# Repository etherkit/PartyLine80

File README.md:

# Party Line 80

## All-Discrete 80 Meter CW QRP Transceiver

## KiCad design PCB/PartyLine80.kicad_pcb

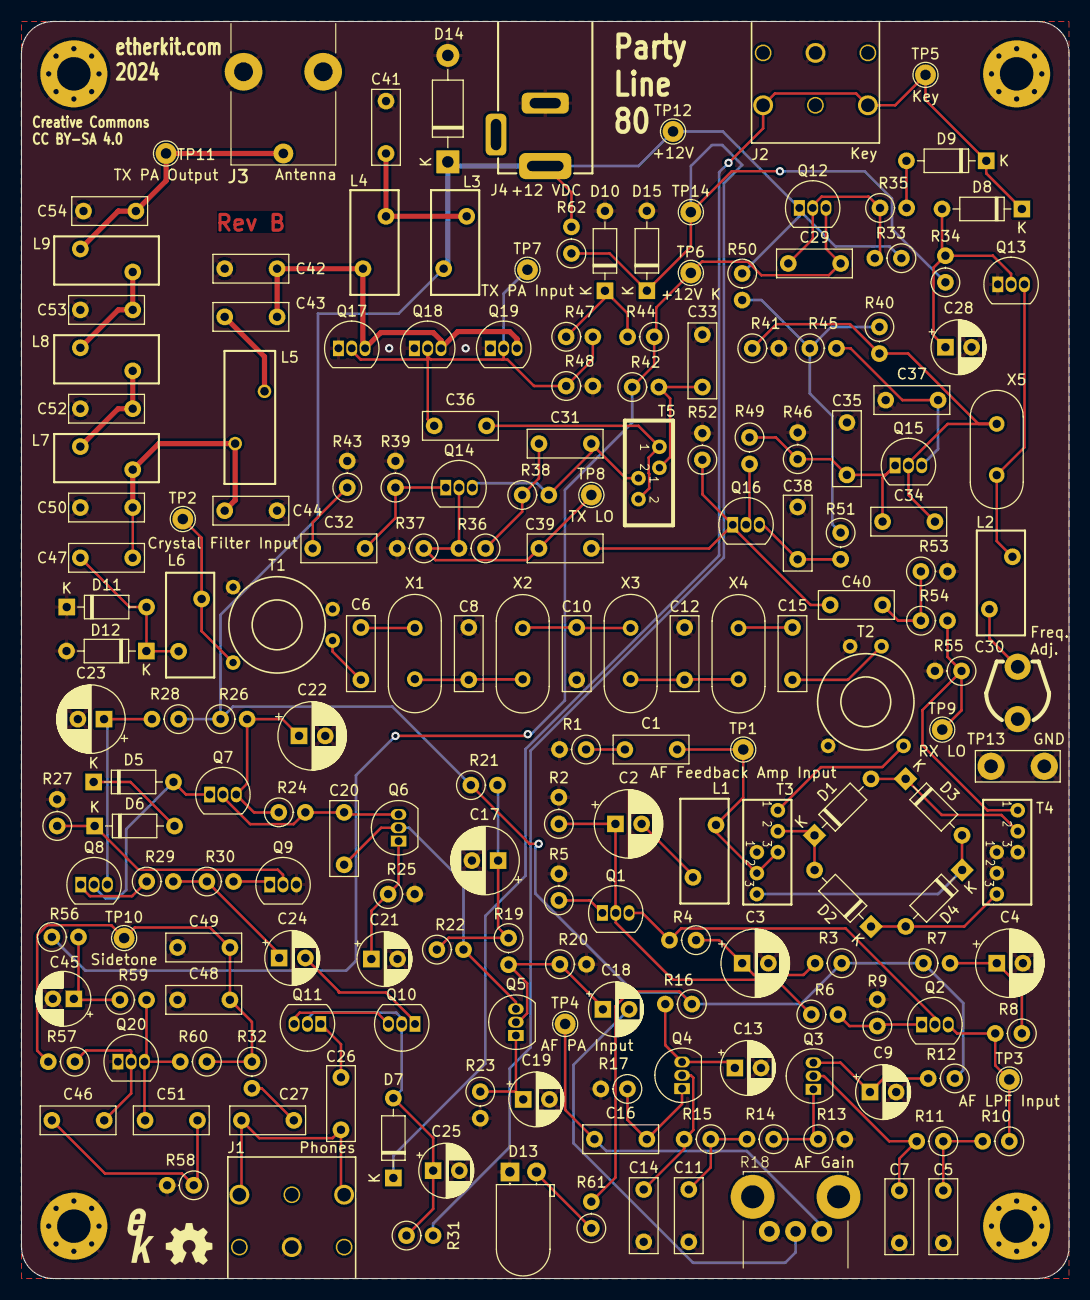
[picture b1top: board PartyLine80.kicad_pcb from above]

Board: 2 copper layers, 100.0 x 120.0 mm, 194 parts (0 on the bottom side), 95 nets.

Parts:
C1, C29, C31, C32, C33, C36, C37, C38, C39, C40, C41, C46, C48, C49, C51: 100n; C_Rect_L7.0mm_W2.5mm_P5.00mm
C2: 220u; CP_Radial_D6.3mm_P2.50mm
C3, C4, C17, C22, C23: 100u; CP_Radial_D6.3mm_P2.50mm
C5, C7, C11, C14: 10n; C_Rect_L7.0mm_W2.5mm_P5.00mm
C6, C10, C15: 25; C_Rect_L7.0mm_W2.5mm_P5.00mm
C8, C12: 20; C_Rect_L7.0mm_W2.5mm_P5.00mm
C9, C13, C19, C21, C24: 10u; CP_Radial_D5.0mm_P2.50mm
C16: 1u Film; C_Rect_L7.0mm_W2.5mm_P5.00mm
C18: 1u Film; CP_Radial_D5.0mm_P2.50mm
C20: 2.2n; C_Rect_L7.0mm_W2.5mm_P5.00mm
C25, C28: 1u; CP_Radial_D5.0mm_P2.50mm
C26, C27: 560n Film; C_Rect_L7.0mm_W2.5mm_P5.00mm
C30: 45p; TRIMCAP-MURATA
C34, C35, C42: 560p; C_Rect_L7.0mm_W2.5mm_P5.00mm
C43: 360p; C_Rect_L7.0mm_W2.5mm_P5.00mm
C44: 1.5n; C_Rect_L7.0mm_W2.5mm_P5.00mm
C45: 1u; CP_Radial_D5.0mm_P2.00mm
C47: 82p; C_Rect_L7.0mm_W2.5mm_P5.00mm
C50, C54: 270p; C_Rect_L7.0mm_W2.5mm_P5.00mm
C52, C53: 1n; C_Rect_L7.0mm_W2.5mm_P5.00mm
D1, D2, D3, D4, D5, D6, D7, D8, D9, D11, D12: 1N4148; D_DO-35_SOD27_P7.62mm_Horizontal
D10, D15: 1N5237B; D_DO-35_SOD27_P7.62mm_Horizontal
D13: LED; LED_D5.0mm_Horizontal_O1.27mm_Z3.0mm
D14: SB140; D_DO-41_SOD81_P10.16mm_Horizontal
G1: LOGO; EtherkitLogoSmall
H1, H2, H3, H4: MountingHole_Pad; MountingHole_3.2mm_M3_Pad_Via
J1: Phones; Kycon_STX-3120-3B
J2: Key; Kycon_STX-3120-3B
J3: BNC; Molex_0731713150
J4: 2.1 mm Barrel Jack; CUI_PJ-202AH
L1: FT37-43 25T; T37-V
L2: T37-2 22T; T37-V
L3, L4: FT37-43 10T; T37-V
L5: T50-2 36T; T50-V
L6: FT37-61 20T; T37-V
L7, L9: T37-2 20T; T37-V
L8: T37-2 26T; T37-V
Q1, Q2, Q3, Q4, Q5, Q6, Q7, Q8, Q14, Q15, Q16, Q20: 2N4401; TO-92_Inline
Q9, Q12: 2N4403; TO-92_Inline
Q10, Q11, Q13, Q17, Q18, Q19: 2N7000; TO-92_Inline
R1, R7, R26: 51; R_Axial_DIN0207_L6.3mm_D2.5mm_P2.54mm_Vertical
R2, R6: 1.8k; R_Axial_DIN0207_L6.3mm_D2.5mm_P2.54mm_Vertical
R3, R53, R55: 150; R_Axial_DIN0207_L6.3mm_D2.5mm_P2.54mm_Vertical
R4, R62: 1k; R_Axial_DIN0207_L6.3mm_D2.5mm_P2.54mm_Vertical
R5: 22; R_Axial_DIN0207_L6.3mm_D2.5mm_P2.54mm_Vertical
R8: 680; R_Axial_DIN0207_L6.3mm_D2.5mm_P2.54mm_Vertical
R9, R32, R33, R50, R52: 220; R_Axial_DIN0207_L6.3mm_D2.5mm_P2.54mm_Vertical
R10, R11, R13, R14, R15, R17, R21: 4.7k; R_Axial_DIN0207_L6.3mm_D2.5mm_P2.54mm_Vertical
R12, R16, R39, R45, R51: 100; R_Axial_DIN0207_L6.3mm_D2.5mm_P2.54mm_Vertical
R18: 1k Audio; Bournes_PTV09A
R19: 47k; R_Axial_DIN0207_L6.3mm_D2.5mm_P2.54mm_Vertical
R20, R40, R41, R44: 10k; R_Axial_DIN0207_L6.3mm_D2.5mm_P2.54mm_Vertical
R22, R24, R25, R35, R37: 2.2k; R_Axial_DIN0207_L6.3mm_D2.5mm_P2.54mm_Vertical
R23, R27, R46, R49: 470; R_Axial_DIN0207_L6.3mm_D2.5mm_P2.54mm_Vertical
R28: 10; R_Axial_DIN0207_L6.3mm_D2.5mm_P2.54mm_Vertical
R29, R30: 1; R_Axial_DIN0207_L6.3mm_D2.5mm_P2.54mm_Vertical
R31, R34: 100k; R_Axial_DIN0207_L6.3mm_D2.5mm_P2.54mm_Vertical
R36: 1.5k; R_Axial_DIN0207_L6.3mm_D2.5mm_P2.54mm_Vertical
R38: 3k; R_Axial_DIN0207_L6.3mm_D2.5mm_P2.54mm_Vertical
R42, R56: 47; R_Axial_DIN0207_L6.3mm_D2.5mm_P2.54mm_Vertical
R43: 4.7; R_Axial_DIN0207_L6.3mm_D2.5mm_P2.54mm_Vertical
R47, R48, R57, R59, R60, R61: 3.3k; R_Axial_DIN0207_L6.3mm_D2.5mm_P2.54mm_Vertical
R54: 36; R_Axial_DIN0207_L6.3mm_D2.5mm_P2.54mm_Vertical
R58: 330; R_Axial_DIN0207_L6.3mm_D2.5mm_P2.54mm_Vertical
SYM1: Logo_Open_Hardware_Small; OSHWLogo4mm
T1, T2: FT37-43 3T:21T; T37-STEPDOWN
T3, T4: FT37-43 10T Trifilar; T37-V-TRIFILARXFMR
T5: FT37-43 10T Bifilar; T37-V-BIFILARXFMR
TP1: AF Feedback Amp Input; TestPoint_THTPad_D2.0mm_Drill1.0mm
TP2: Crystal Filter Input; TestPoint_THTPad_D2.0mm_Drill1.0mm
TP3: AF LPF Input; TestPoint_THTPad_D2.0mm_Drill1.0mm
TP4: AF PA Input; TestPoint_THTPad_D2.0mm_Drill1.0mm
TP5: Key; TestPoint_THTPad_D2.0mm_Drill1.0mm
TP6: +12V K; TestPoint_THTPad_D2.0mm_Drill1.0mm
TP7: TX PA Input; TestPoint_THTPad_D2.0mm_Drill1.0mm
TP8: TX LO; TestPoint_THTPad_D2.0mm_Drill1.0mm
TP9: RX LO; TestPoint_THTPad_D2.0mm_Drill1.0mm
TP10: Sidetone; TestPoint_THTPad_D2.0mm_Drill1.0mm
TP11: TX PA Output; TestPoint_THTPad_D2.0mm_Drill1.0mm
TP12: +12V; TestPoint_THTPad_D2.0mm_Drill1.0mm
TP13: GND; TestPoint_Bridge_Pitch5.08mm_Drill1.3mm
TP14: +3.3V; TestPoint_THTPad_D2.0mm_Drill1.0mm
X1, X2, X3, X4, X5: 3.582 MHz; Crystal_HC49-U_Vertical

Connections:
+3.3V: D15.2 (K), R31.2, R34.1, R62.1, TP14.1
+12V: D14.1 (K), J4.1, L3.1, Q12.1 (E), R3.1, R7.1, R12.1, R16.1, R21.1, R26.1, R28.1, R33.1, R50.1, R61.2, R62.2, TP12.1
+12V K: C29.2, Q12.3 (C), R42.1, R44.1, R56.1, TP6.1
GND: C3.2, C4.2, C5.1, C7.1, C8.1, C9.2, C10.1, C11.1, C12.1, C13.2, C14.1, C17.2, C19.2, C21.2, C22.2, C23.2, C25.2, C28.2, C30.2, C33.1, C35.1, C37.1, C38.1, C41.1, C42.1, C44.1, C45.2, C48.1, C49.1, C50.1, C52.1, C53.1, C54.1, D10.1 (A), D11.1 (K), D12.2 (A), D13.1 (K), D14.2 (A), D15.1 (A), H1.1, H2.1, H3.1, H4.1, J1.S, J2.S, J3.2 (Ext), J4.2, Q9.3 (C), Q13.1 (S), Q17.1 (S), Q18.1 (S), Q19.1 (S), Q20.1 (E), R1.2, R2.2, R5.2, R9.2, R13.2, R17.2, R18.3, R20.2, R23.2, R25.2, R27.2, R37.2, R39.2, R41.2, R43.2, R46.2, R48.2, R52.2, R53.2, R55.2, R58.2, T1.2, T1.4, T2.2, T2.4, T3.2, T4.2, T4.4, T4.5 (3), TP13.1
unnamed: C1.1, R1.1
unnamed: C1.2, L1.1, T3.4, T3.5 (3), TP1.1
unnamed: C2.2, L1.2
unnamed: C3.1, R3.2, R4.1
unnamed: C4.1, R7.2, R8.1
unnamed: C5.2, R10.2, R11.1
unnamed: C6.1, T1.1
unnamed: C6.2, X1.1
unnamed: C8.2, X1.2, X2.1
unnamed: C10.2, X2.2, X3.1
unnamed: C11.2, R14.2, R15.1
unnamed: C12.2, X3.2, X4.1
unnamed: C15.1, X4.2
unnamed: C15.2, T2.1
unnamed: C16.1, R18.1, TP4.1
unnamed: C17.1, R19.1, R21.2, R22.1
unnamed: C18.2, R18.2
unnamed: C24.1, R29.2, R30.1
unnamed: C26.1, C27.1, J1.R, J1.T
unnamed: C27.2, R32.2
unnamed: C30.1, L2.1
unnamed: C31.2, R36.1, R38.1
unnamed: C32.1, R43.1
unnamed: C33.2, R42.2, T5.3
unnamed: C36.2, T5.1, T5.4
unnamed: C40.1, R53.1, R54.1
unnamed: C41.2, L3.2, L4.1
unnamed: C43.1, L5.1
unnamed: C44.2, C47.2, C50.2, L5.2, L7.1
unnamed: C45.1, R56.2, R59.1
unnamed: C46.1, C51.2, R58.1
unnamed: C52.2, L7.2, L8.1
unnamed: C53.2, L8.2, L9.1
unnamed: D1.1, D2.2, T3.3
unnamed: D1.2, D3.1, T4.3
unnamed: D2.1, D4.2, T4.6 (4)
unnamed: D3.2, D4.1, T3.6 (4)
unnamed: D5.2 (A), Q7.1 (E), Q8.2 (B)
unnamed: D5.1 (K), D6.2 (A)
unnamed: D6.1 (K), Q9.2 (B), R27.1
unnamed: C25.1, D7.2 (A), Q10.2 (G), Q11.2 (G), R31.1
unnamed: C28.1, D8.2 (A), Q13.2 (G), R34.2
unnamed: D9.2 (A), R35.2
unnamed: D10.2 (K), R44.2, R47.1
unnamed: C47.1, D11.2 (A), D12.1 (K), L6.1
unnamed: D13.2 (A), R61.1
unnamed: C54.2, J3.1 (In), L9.2, TP11.1
unnamed: C2.1, Q1.2 (B), R2.1, R6.1
unnamed: Q1.3 (C), Q2.2 (B), R4.2
unnamed: Q1.1 (E), R5.1
unnamed: Q2.3 (C), R8.2, R10.1, TP3.1
unnamed: Q2.1 (E), R6.2, R9.1
unnamed: C7.2, Q3.2 (B), R11.2
unnamed: C9.1, Q3.3 (C), R12.2
unnamed: Q3.1 (E), R13.1, R14.1
unnamed: C14.2, Q4.2 (B), R15.2
unnamed: C13.1, Q4.3 (C), R16.2
unnamed: C16.2, Q4.1 (E), R17.1
unnamed: C18.1, Q5.2 (B), R19.2, R20.1
unnamed: C20.2, Q5.3 (C), Q6.2 (B), R22.2
unnamed: C19.1, Q5.1 (E), R23.1
unnamed: C20.1, Q6.3 (C), Q7.2 (B), R24.2
unnamed: C21.1, Q6.1 (E), R25.1
unnamed: C22.1, Q7.3 (C), R24.1, R26.2
unnamed: C23.1, Q8.3 (C), R28.2
unnamed: Q8.1 (E), R29.1
unnamed: Q9.1 (E), R30.2
unnamed: Q10.3 (D), Q11.3 (D)
unnamed: C24.2, Q10.1 (S)
unnamed: C26.2, Q11.1 (S)
unnamed: C29.1, Q12.2 (B), R33.2, R35.1
unnamed: L2.2, Q13.3 (D), X5.1
unnamed: C31.1, Q14.3 (C), R38.2, T5.2
unnamed: C32.2, Q14.1 (E), R39.1
unnamed: C34.2, Q15.2 (B), R40.2, R41.1, X5.2
unnamed: C37.2, Q15.3 (C), R45.2
unnamed: C34.1, C35.2, Q15.1 (E), R46.1, R49.1
unnamed: Q16.2 (B), R49.2
unnamed: C38.2, Q16.3 (C), R51.2
unnamed: C39.2, C40.2, Q16.1 (E), R52.1
unnamed: C42.2, C43.2, L4.2, Q17.3 (D), Q18.3 (D), Q19.3 (D)
unnamed: C36.1, Q17.2 (G), Q18.2 (G), Q19.2 (G), R47.2, R48.1, TP7.1
unnamed: C46.2, Q20.2 (B), R57.1
unnamed: C51.1, Q20.3 (C), R59.2, R60.2
unnamed: R40.1, R45.1, R50.2, R51.1
unnamed: T2.3, T3.1
RX: L6.2, T1.3, TP2.1
RX LO: R54.2, R55.1, T4.1, TP9.1
Sidetone: C48.2, C49.2, R32.1, R57.2, R60.1, TP10.1
TX LO: C39.1, Q14.2 (B), R36.2, R37.1, TP8.1
~KEY: D7.1 (K), D8.1 (K), D9.1 (K), J2.R, J2.T, TP5.1

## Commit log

2024-01-19 Add basic build instructions
2024-05-25 Party Line 80 PCB Rev B
2024-05-25 Update rendering of PCB

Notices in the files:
PCB/PartyLine80.kicad_pcb:
Creative Commons
CC BY-SA 4.0
